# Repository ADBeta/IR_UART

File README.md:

# USB IR UART Adapter
Converts USB to UART, then to Inverted or Normal IR Signalling.  
Uses any generic IR LED and IR Phototransistor.

---
(c) ADBeta 2026

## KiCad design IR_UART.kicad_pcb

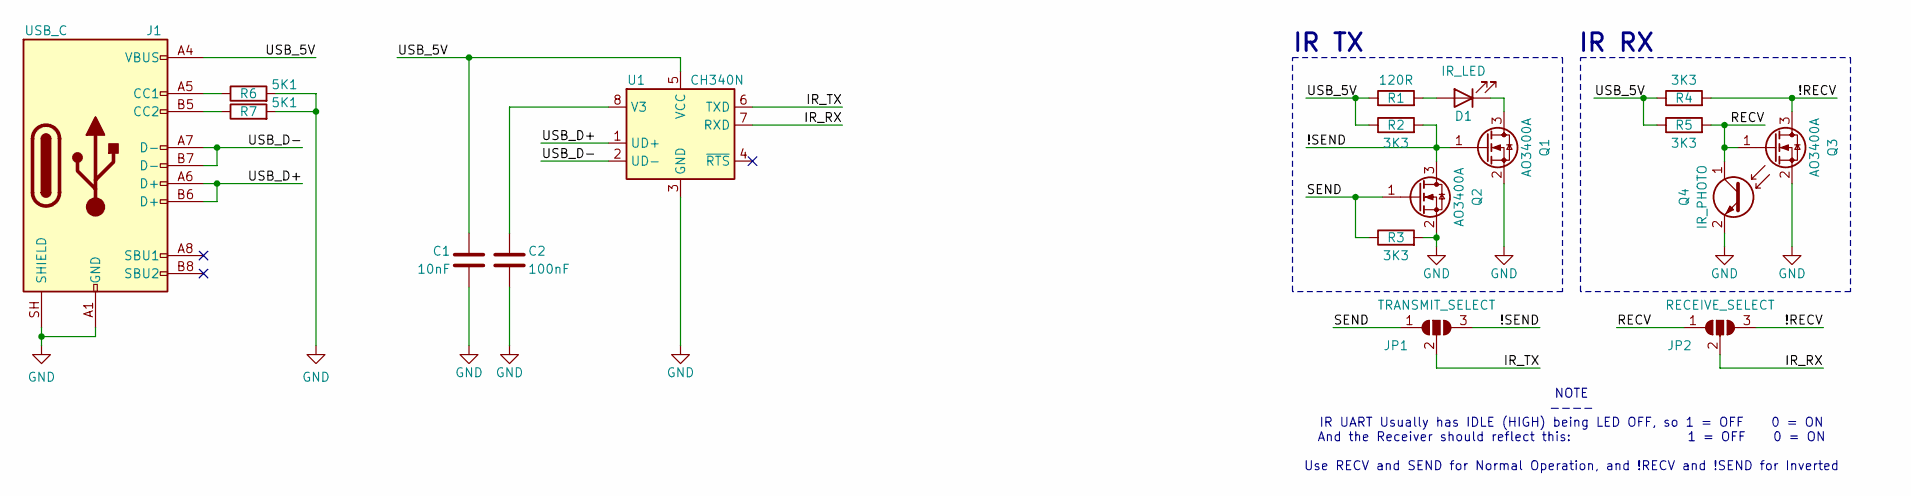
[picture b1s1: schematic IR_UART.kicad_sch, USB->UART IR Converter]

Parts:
C1: 10nF; C_0603_1608Metric
C2: 100nF; C_0603_1608Metric
D1: IR_LED; LED_D3.0mm_Clear
J1: USB_C; USB_C_Receptacle_G-Switch_GT-USB-7010ASV
JP1: TRANSMIT_SELECT; SolderJumper-3_P1.3mm_Open_RoundedPad1.0x1.5mm
JP2: RECEIVE_SELECT; SolderJumper-3_P1.3mm_Open_RoundedPad1.0x1.5mm
Q1, Q2, Q3: AO3400A; SOT-23
Q4: IR_PHOTO; LED_D3.0mm_Clear
R1: 120R; R_0603_1608Metric
R2, R3, R4, R5: 3K3; R_0603_1608Metric
R6, R7: 5K1; R_0603_1608Metric
U1: CH340N; JEITA_SOIC-8_3.9x4.9mm_P1.27mm

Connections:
/!RECV: JP2.3 (B), Q3.3 (D), R4.2
/!SEND: JP1.3 (B), Q1.1 (G), Q2.3 (D), R2.2
/IR_RX: JP2.2 (C), U1.7 (RXD)
/IR_TX: JP1.2 (C), U1.6 (TXD)
/RECV: JP2.1 (A), Q3.1 (G), Q4.1 (C), R5.2
/SEND: JP1.1 (A), Q2.1 (G), R3.1
/USB_5V: C1.1, J1.A4 (VBUS), J1.A9 (VBUS), J1.B4 (VBUS), J1.B9 (VBUS), R1.1, R2.1, R4.1, R5.1, U1.5 (VCC)
/USB_D+: J1.A6 (D+), J1.B6 (D+), U1.1 (UD+)
/USB_D-: J1.A7 (D-), J1.B7 (D-), U1.2 (UD-)
GND: C1.2, C2.2, J1.A1 (GND), J1.A12 (GND), J1.B1 (GND), J1.B12 (GND), J1.SH (SHIELD), Q1.2 (S), Q2.2 (S), Q3.2 (S), Q4.2 (E), R3.2, R6.2, R7.2, U1.3 (GND)
unnamed: D1.2 (A), R1.2
unnamed: D1.1 (K), Q1.3 (D)
unnamed: J1.A5 (CC1), R6.1
unnamed: J1.B5 (CC2), R7.1
unnamed: C2.1, U1.8 (V3)

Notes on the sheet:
IR TX
NOTE ---- IR UART Usually has IDLE (HIGH) being LED OFF, so 1 = OFF 0 = ON And the Receiver should reflect this: 1 = OFF 0 = ON Use RECV and SEND for Normal Operation, and !RECV and !SEND for Inverted
IR RX

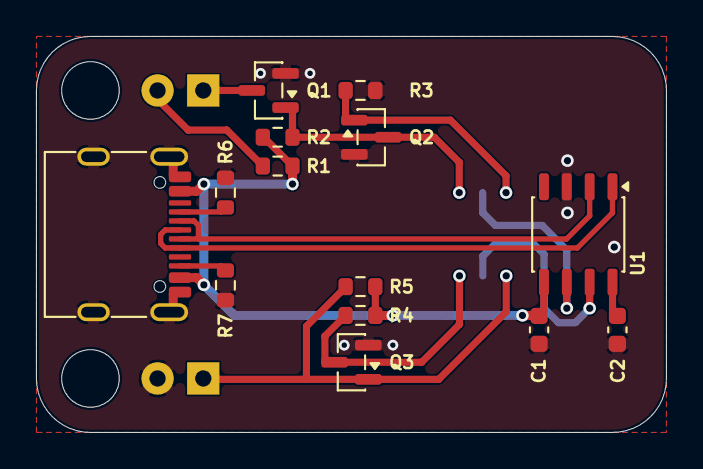
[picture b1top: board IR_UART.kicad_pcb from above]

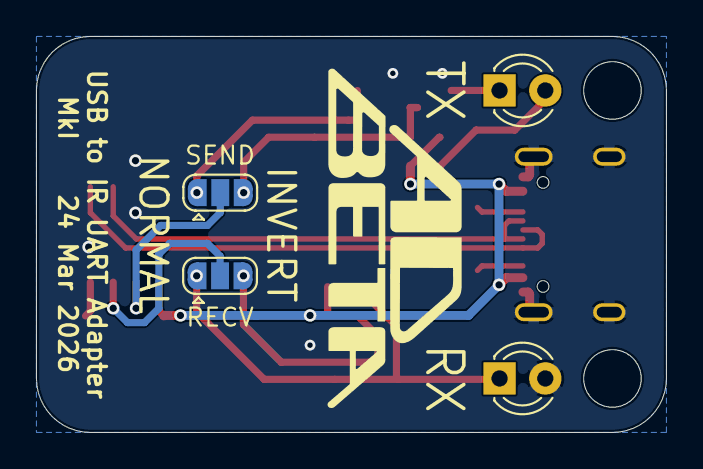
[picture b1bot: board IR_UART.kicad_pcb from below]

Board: 2 copper layers, 35.0 x 22.0 mm, 18 parts (4 on the bottom side), 15 nets.

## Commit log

2026-03-24 MkI PCB Done
2026-04-02 Removed and ignored .history
